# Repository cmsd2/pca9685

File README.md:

PCA9685 Breakout Board
======================

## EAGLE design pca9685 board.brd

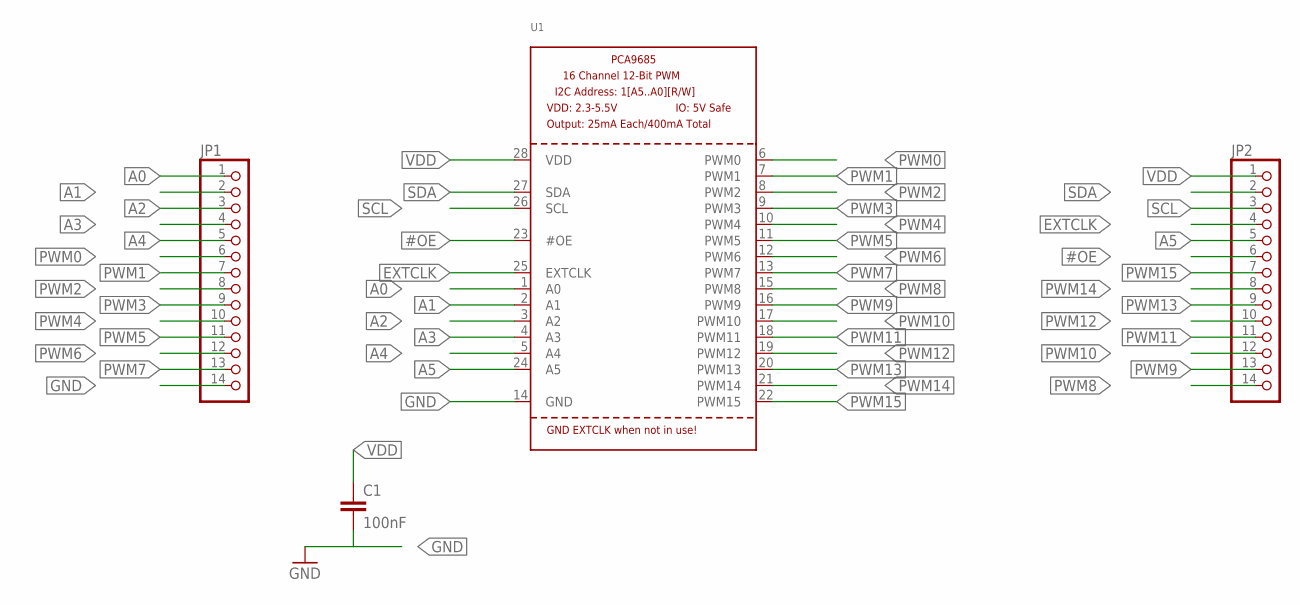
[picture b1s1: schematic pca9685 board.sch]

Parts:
C1: 100nF; C0805
JP1, JP2: PINHD-1X14; 1X14
U1: PCA9685; TSSOP28

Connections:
#OE: JP2.6, U1.23 (#OE)
A0: JP1.1, U1.1 (A0)
A1: JP1.2, U1.2 (A1)
A2: JP1.3, U1.3 (A2)
A3: JP1.4, U1.4 (A3)
A4: JP1.5, U1.5 (A4)
A5: JP2.5, U1.24 (A5)
EXTCLK: JP2.4, U1.25 (EXTCLK)
GND: C1.2, JP1.14, U1.14 (GND)
PWM0: JP1.6, U1.6 (PWM0)
PWM1: JP1.7, U1.7 (PWM1)
PWM2: JP1.8, U1.8 (PWM2)
PWM3: JP1.9, U1.9 (PWM3)
PWM4: JP1.10, U1.10 (PWM4)
PWM5: JP1.11, U1.11 (PWM5)
PWM6: JP1.12, U1.12 (PWM6)
PWM7: JP1.13, U1.13 (PWM7)
PWM8: JP2.14, U1.15 (PWM8)
PWM9: JP2.13, U1.16 (PWM9)
PWM10: JP2.12, U1.17 (PWM10)
PWM11: JP2.11, U1.18 (PWM11)
PWM12: JP2.10, U1.19 (PWM12)
PWM13: JP2.9, U1.20 (PWM13)
PWM14: JP2.8, U1.21 (PWM14)
PWM15: JP2.7, U1.22 (PWM15)
SCL: JP2.3, U1.26 (SCL)
SDA: JP2.2, U1.27 (SDA)
VDD: C1.1, JP2.1, U1.28 (VDD)

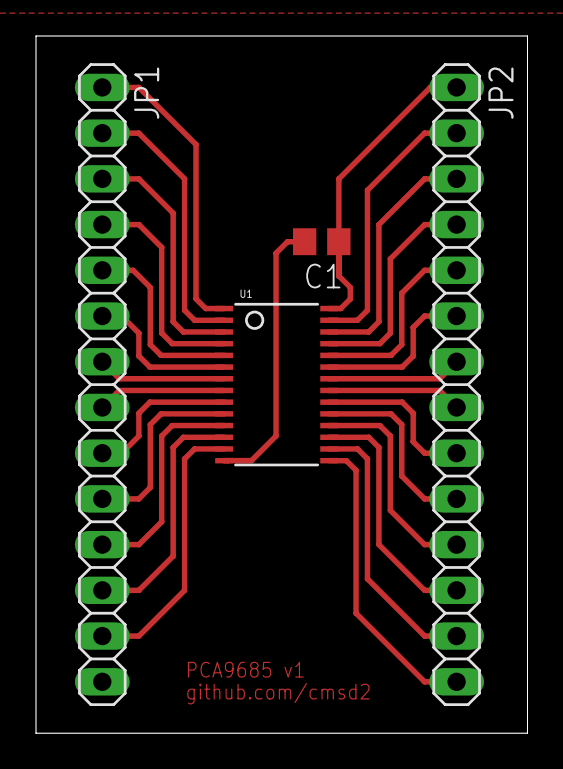
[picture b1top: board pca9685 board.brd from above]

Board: 2 copper layers, 27.3 x 38.7 mm, 4 parts (0 on the bottom side), 28 nets.

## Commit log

2015-05-17 pca9685 v1
2015-05-17 add license
2015-05-17 add readme and picture
2015-05-17 add schematic picture
2015-05-17 higher res
2015-05-17 even higher res
2015-05-20 don't really need such fat power lines
2015-05-20 update image with smaller power traces
